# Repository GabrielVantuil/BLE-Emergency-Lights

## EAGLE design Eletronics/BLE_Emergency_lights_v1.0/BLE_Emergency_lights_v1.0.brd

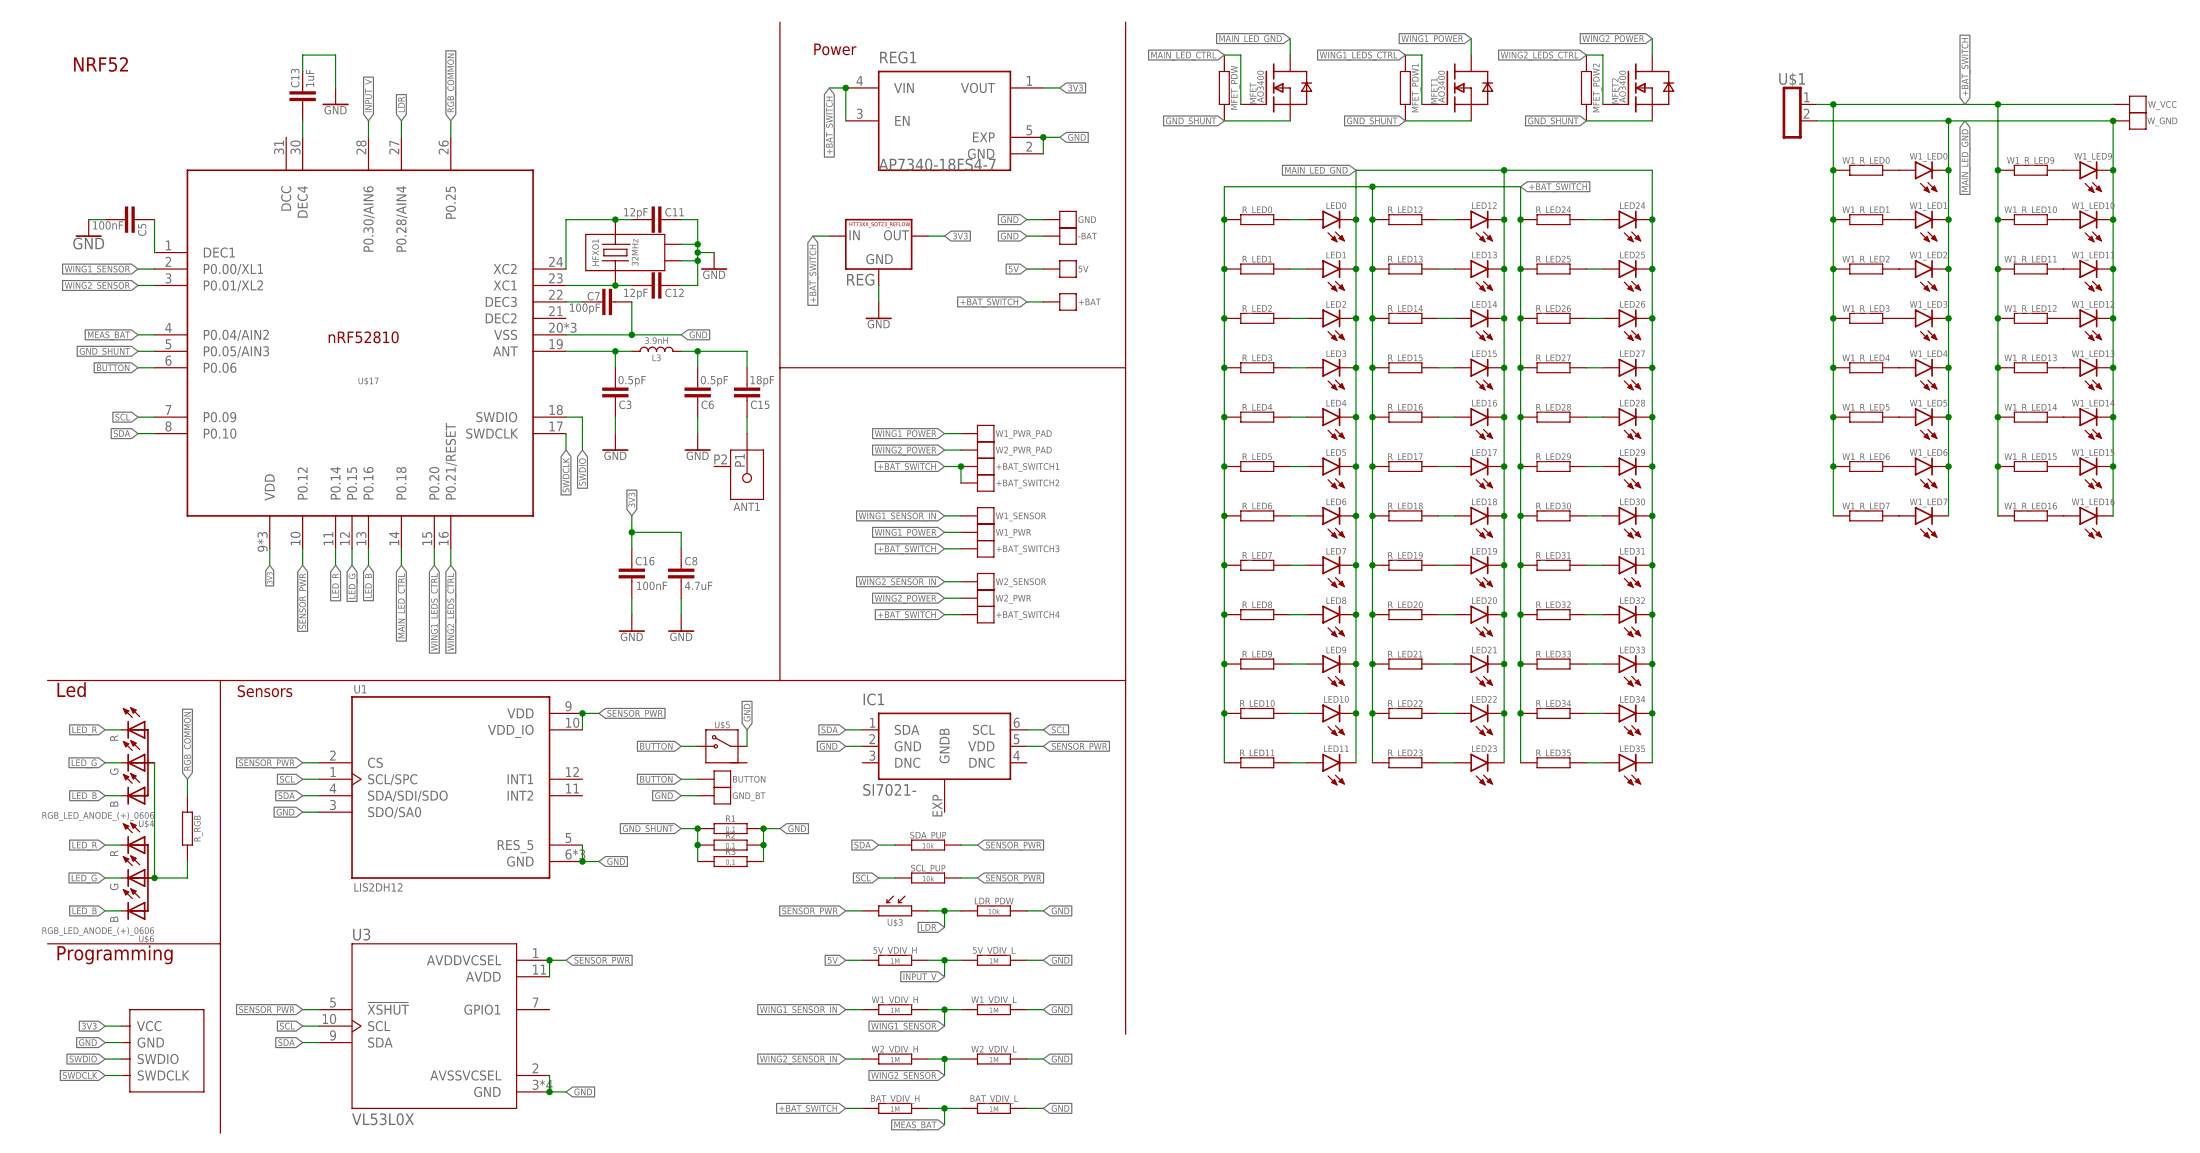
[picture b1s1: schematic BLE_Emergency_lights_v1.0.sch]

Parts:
5V: PAD_50X100MIL
5V_VDIV_H, 5V_VDIV_L: 1M; 0402-RES
+BAT: PAD_50X100MIL
+BAT_SWITCH1, +BAT_SWITCH2: PAD_50X100MIL
+BAT_SWITCH3, +BAT_SWITCH4: SMD_VERTICAL_POGOPIN_0.8MM; POGOPIN_0.8T
-BAT: PAD_50X100MIL
ANT1: ANT3216LL00R2400A
BAT_VDIV_H: 1M; 0402-RES
BAT_VDIV_L: 1M; 0402-RES
BUTTON: PAD_50X100MIL
C3, C6: 0.5pF; 0201_LARGE_FP-CAP
C5, C16: 100nF; 0201_LARGE_FP-CAP
C7: 100pF; 0201_LARGE_FP-CAP
C8: 4.7uF; 0402-CAP
C11, C12: 12pF; 0201_LARGE_FP-CAP
C13: 1uF; 0201_LARGE_FP-CAP
C15: 18pF; 0201_LARGE_FP-CAP
GND: PAD_50X100MIL
GND_BT: PAD_50X100MIL
HFXO1: 32MHz; XTAL_CX2016DB16000D0WZRC1
IC1: SI7021-; DFN6-3X3
L3: 3.9nH; 0201_LARGE_FP-CAP
LDR_PDW: 10k; 0402-RES
LED0, LED1, LED2, LED3, LED4, LED5, LED6, LED7, LED8, LED9, LED10, LED11, LED12, LED13, LED14, LED15, LED16, LED17, LED18, LED19, LED20, LED21, LED22, LED23, LED24, LED25, LED26, LED27, LED28, LED29, LED30, LED31, LED32, LED33, LED34, LED35: LED_1210; 1210
MFET, MFET1, MFET2: AO3400; SOT23-3
MFET_PDW, MFET_PDW1, MFET_PDW2: RESISTOR0402-RES; 0402-RES
R1, R2, R3: 0,1; 1206
REG: HT73XX_SOT23_REFLOW; SOT23-R
REG1: AP7340-18FS4-7; VREG_AP7340-18FS4-7
R_LED0, R_LED1, R_LED2, R_LED3, R_LED4, R_LED5, R_LED6, R_LED7, R_LED8, R_LED9, R_LED10, R_LED11, R_LED12, R_LED13, R_LED14, R_LED15, R_LED16, R_LED17, R_LED18, R_LED19, R_LED20, R_LED21, R_LED22, R_LED23, R_LED24, R_LED25, R_LED26, R_LED27, R_LED28, R_LED29, R_LED30, R_LED31, R_LED32, R_LED33, R_LED34, R_LED35: RESISTOR0603-RES; 0603-RES
R_RGB: RESISTOR_0201_LARGE_FP; 0201_LARGE_FT-RES
SCL_PUP: 10k; 0402-RES
SDA_PUP: 10k; 0402-RES
U1: LIS2DH12; SENSOR_LIS2DH12
U3: VL53L0X; SENSOR_VL53L0X
U$1: RING_PAD_02_4X6; 2X_RING_PAD_4X6
U$3: LDR_5MM
U$4, U$6: RGB_LED_ANODE_(+)_0606; LED_RGB_0606
U$5: PUSHBUTTON_2X4X3.5; 2X4X3.5MM
U$9: GV_SWD_4P; GV_SWD_1.27MM_4P_SEMI_SMD
U$17: NRF52810-QFN32; QFN32-SMALL_PADS2
W1_LED0, W1_LED1, W1_LED2, W1_LED3, W1_LED4, W1_LED5, W1_LED6, W1_LED7, W1_LED9, W1_LED10, W1_LED11, W1_LED12, W1_LED13, W1_LED14, W1_LED15, W1_LED16: LED_1210; 1210
W1_PWR, W1_SENSOR, W2_PWR, W2_SENSOR: SMD_VERTICAL_POGOPIN_0.8MM; POGOPIN_0.8T
W1_PWR_PAD, W2_PWR_PAD: PAD_50X100MIL
W1_R_LED0, W1_R_LED1, W1_R_LED2, W1_R_LED3, W1_R_LED4, W1_R_LED5, W1_R_LED6, W1_R_LED7, W1_R_LED9, W1_R_LED10, W1_R_LED11, W1_R_LED12, W1_R_LED13, W1_R_LED14, W1_R_LED15, W1_R_LED16: RESISTOR0603-RES; 0603-RES
W1_VDIV_H, W1_VDIV_L, W2_VDIV_H, W2_VDIV_L: 1M; 0402-RES
W_GND: PINH1X01_0.8MM; 0.8MM
W_VCC: PINH1X01_0.8MM; 0.8MM

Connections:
3V3: C8.1, C16.1, REG.2 (3.OUT), REG1.1 (VOUT), U$9.VCC, U$17.9 (VDD), U$17.25 (VDD), U$17.32 (VDD)
5V: 5V.P$1, 5V_VDIV_H.2
+BAT_SWITCH: +BAT.P$1, +BAT_SWITCH1.P$1, +BAT_SWITCH2.P$1, +BAT_SWITCH3.P$1, +BAT_SWITCH4.P$1, BAT_VDIV_H.2, REG.3 (1.IN), REG1.3 (EN), REG1.4 (VIN), R_LED0.1, R_LED1.1, R_LED2.1, R_LED3.1, R_LED4.1, R_LED5.1, R_LED6.1, R_LED7.1, R_LED8.1, R_LED9.1, R_LED10.1, R_LED11.1, R_LED12.1, R_LED13.1, R_LED14.1, R_LED15.1, R_LED16.1, R_LED17.1, R_LED18.1, R_LED19.1, R_LED20.1, R_LED21.1, R_LED22.1, R_LED23.1, R_LED24.1, R_LED25.1, R_LED26.1, R_LED27.1, R_LED28.1, R_LED29.1, R_LED30.1, R_LED31.1, R_LED32.1, R_LED33.1, R_LED34.1, R_LED35.1, U$1.1, W1_R_LED0.1, W1_R_LED1.1, W1_R_LED2.1, W1_R_LED3.1, W1_R_LED4.1, W1_R_LED5.1, W1_R_LED6.1, W1_R_LED7.1, W1_R_LED9.1, W1_R_LED10.1, W1_R_LED11.1, W1_R_LED12.1, W1_R_LED13.1, W1_R_LED14.1, W1_R_LED15.1, W1_R_LED16.1, W_VCC.P$1
ANT1: C3.1, L3.1, U$17.19 (ANT)
ANT2: C6.1, C15.1, L3.2
BUTTON: BUTTON.P$1, U$5.1, U$17.6 (P0.06)
GND: 5V_VDIV_L.2, -BAT.P$1, BAT_VDIV_L.2, C3.2, C5.2, C6.2, C7.1, C8.2, C11.1, C12.1, C13.1, C16.2, GND.P$1, GND_BT.P$1, HFXO1.2, HFXO1.4, IC1.2 (GND), LDR_PDW.2, R1.2, R2.2, R3.2, REG.1 (2.GND), REG1.2 (GND), REG1.5 (EXP), U1.3 (SDO/SA0), U1.5 (RES_5), U1.6 (GND), U1.7 (GND), U1.8 (GND), U3.2 (AVSSVCSEL), U3.3 (GND), U3.4 (GND), U3.6 (GND), U3.12 (GND), U$5.2, U$9.GND, U$17.20 (VSS), U$17.29 (VSS), U$17.EXP (VSS), W1_VDIV_L.2, W2_VDIV_L.2
GND_SHUNT: MFET.2 (S), MFET1.2 (S), MFET2.2 (S), MFET_PDW.2, MFET_PDW1.2, MFET_PDW2.2, R1.1, R2.1, R3.1, U$17.5 (P0.05/AIN3)
INPUT_V: 5V_VDIV_H.1, 5V_VDIV_L.1, U$17.28 (P0.30/AIN6)
LDR: LDR_PDW.1, U$3.P$2, U$17.27 (P0.28/AIN4)
LED_B: U$4.B (LED_BLUE), U$6.B (LED_BLUE), U$17.13 (P0.16)
LED_G: U$4.G (LED_GREEN), U$6.G (LED_GREEN), U$17.12 (P0.15)
LED_R: U$4.R (LED_RED), U$6.R (LED_RED), U$17.11 (P0.14)
MAIN_LED_CTRL: MFET.1 (G), MFET_PDW.1, U$17.14 (P0.18)
MAIN_LED_GND: LED0.C, LED1.C, LED2.C, LED3.C, LED4.C, LED5.C, LED6.C, LED7.C, LED8.C, LED9.C, LED10.C, LED11.C, LED12.C, LED13.C, LED14.C, LED15.C, LED16.C, LED17.C, LED18.C, LED19.C, LED20.C, LED21.C, LED22.C, LED23.C, LED24.C, LED25.C, LED26.C, LED27.C, LED28.C, LED29.C, LED30.C, LED31.C, LED32.C, LED33.C, LED34.C, LED35.C, MFET.3 (D), U$1.2, W1_LED0.C, W1_LED1.C, W1_LED2.C, W1_LED3.C, W1_LED4.C, W1_LED5.C, W1_LED6.C, W1_LED7.C, W1_LED9.C, W1_LED10.C, W1_LED11.C, W1_LED12.C, W1_LED13.C, W1_LED14.C, W1_LED15.C, W1_LED16.C, W_GND.P$1
MEAS_BAT: BAT_VDIV_H.1, BAT_VDIV_L.1, U$17.4 (P0.04/AIN2)
unnamed: ANT1.P1, C15.2
unnamed: C7.2, U$17.22 (DEC3)
unnamed: LED0.A, R_LED0.2
unnamed: C13.2, U$17.30 (DEC4)
unnamed: LED1.A, R_LED1.2
unnamed: R_RGB.2, U$4.COM (COMMON_ANODE), U$6.COM (COMMON_ANODE)
unnamed: LED2.A, R_LED2.2
unnamed: C12.2, HFXO1.3, U$17.23 (XC1)
unnamed: C11.2, HFXO1.1, U$17.24 (XC2)
unnamed: LED3.A, R_LED3.2
unnamed: C5.1, U$17.1 (DEC1)
unnamed: LED4.A, R_LED4.2
unnamed: LED5.A, R_LED5.2
unnamed: LED6.A, R_LED6.2
unnamed: LED7.A, R_LED7.2
unnamed: LED8.A, R_LED8.2
unnamed: LED9.A, R_LED9.2
unnamed: LED10.A, R_LED10.2
unnamed: LED11.A, R_LED11.2
unnamed: LED12.A, R_LED12.2
unnamed: LED13.A, R_LED13.2
unnamed: LED14.A, R_LED14.2
unnamed: LED15.A, R_LED15.2
unnamed: LED16.A, R_LED16.2
unnamed: LED17.A, R_LED17.2
unnamed: LED18.A, R_LED18.2
unnamed: LED19.A, R_LED19.2
unnamed: LED20.A, R_LED20.2
unnamed: LED21.A, R_LED21.2
unnamed: LED22.A, R_LED22.2
unnamed: LED23.A, R_LED23.2
unnamed: LED24.A, R_LED24.2
unnamed: LED25.A, R_LED25.2
unnamed: LED26.A, R_LED26.2
unnamed: LED27.A, R_LED27.2
unnamed: LED28.A, R_LED28.2
unnamed: LED29.A, R_LED29.2
unnamed: LED30.A, R_LED30.2
unnamed: LED31.A, R_LED31.2
unnamed: LED32.A, R_LED32.2
unnamed: LED33.A, R_LED33.2
unnamed: LED34.A, R_LED34.2
unnamed: LED35.A, R_LED35.2
unnamed: W1_LED0.A, W1_R_LED0.2
unnamed: W1_LED1.A, W1_R_LED1.2
unnamed: W1_LED2.A, W1_R_LED2.2
unnamed: W1_LED3.A, W1_R_LED3.2
unnamed: W1_LED4.A, W1_R_LED4.2
unnamed: W1_LED5.A, W1_R_LED5.2
unnamed: W1_LED6.A, W1_R_LED6.2
unnamed: W1_LED7.A, W1_R_LED7.2
unnamed: W1_LED9.A, W1_R_LED9.2
unnamed: W1_LED10.A, W1_R_LED10.2
unnamed: W1_LED11.A, W1_R_LED11.2
unnamed: W1_LED12.A, W1_R_LED12.2
unnamed: W1_LED13.A, W1_R_LED13.2
unnamed: W1_LED14.A, W1_R_LED14.2
unnamed: W1_LED15.A, W1_R_LED15.2
unnamed: W1_LED16.A, W1_R_LED16.2
RGB_COMMON: R_RGB.1, U$17.26 (P0.25)
SCL: IC1.6 (SCL), SCL_PUP.1, U1.1 (SCL/SPC), U3.10 (SCL), U$17.7 (P0.09)
SDA: IC1.1 (SDA), SDA_PUP.1, U1.4 (SDA/SDI/SDO), U3.9 (SDA), U$17.8 (P0.10)
SENSOR_PWR: IC1.5 (VDD), SCL_PUP.2, SDA_PUP.2, U1.2 (CS), U1.9 (VDD), U1.10 (VDD_IO), U3.1 (AVDDVCSEL), U3.5 (!XSHUT), U3.11 (AVDD), U$3.P$1, U$17.10 (P0.12)
SWDCLK: U$9.SWDCLK, U$17.17 (SWDCLK)
SWDIO: U$9.SWDIO, U$17.18 (SWDIO)
WING1_LEDS_CTRL: MFET1.1 (G), MFET_PDW1.1, U$17.15 (P0.20)
WING1_POWER: MFET1.3 (D), W1_PWR.P$1, W1_PWR_PAD.P$1
WING1_SENSOR: U$17.2 (P0.00/XL1), W1_VDIV_H.1, W1_VDIV_L.1
WING1_SENSOR_IN: W1_SENSOR.P$1, W1_VDIV_H.2
WING2_LEDS_CTRL: MFET2.1 (G), MFET_PDW2.1, U$17.16 (P0.21/RESET)
WING2_POWER: MFET2.3 (D), W2_PWR.P$1, W2_PWR_PAD.P$1
WING2_SENSOR: U$17.3 (P0.01/XL2), W2_VDIV_H.1, W2_VDIV_L.1
WING2_SENSOR_IN: W2_SENSOR.P$1, W2_VDIV_H.2

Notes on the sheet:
NRF52
Led
Sensors
Power
Programming

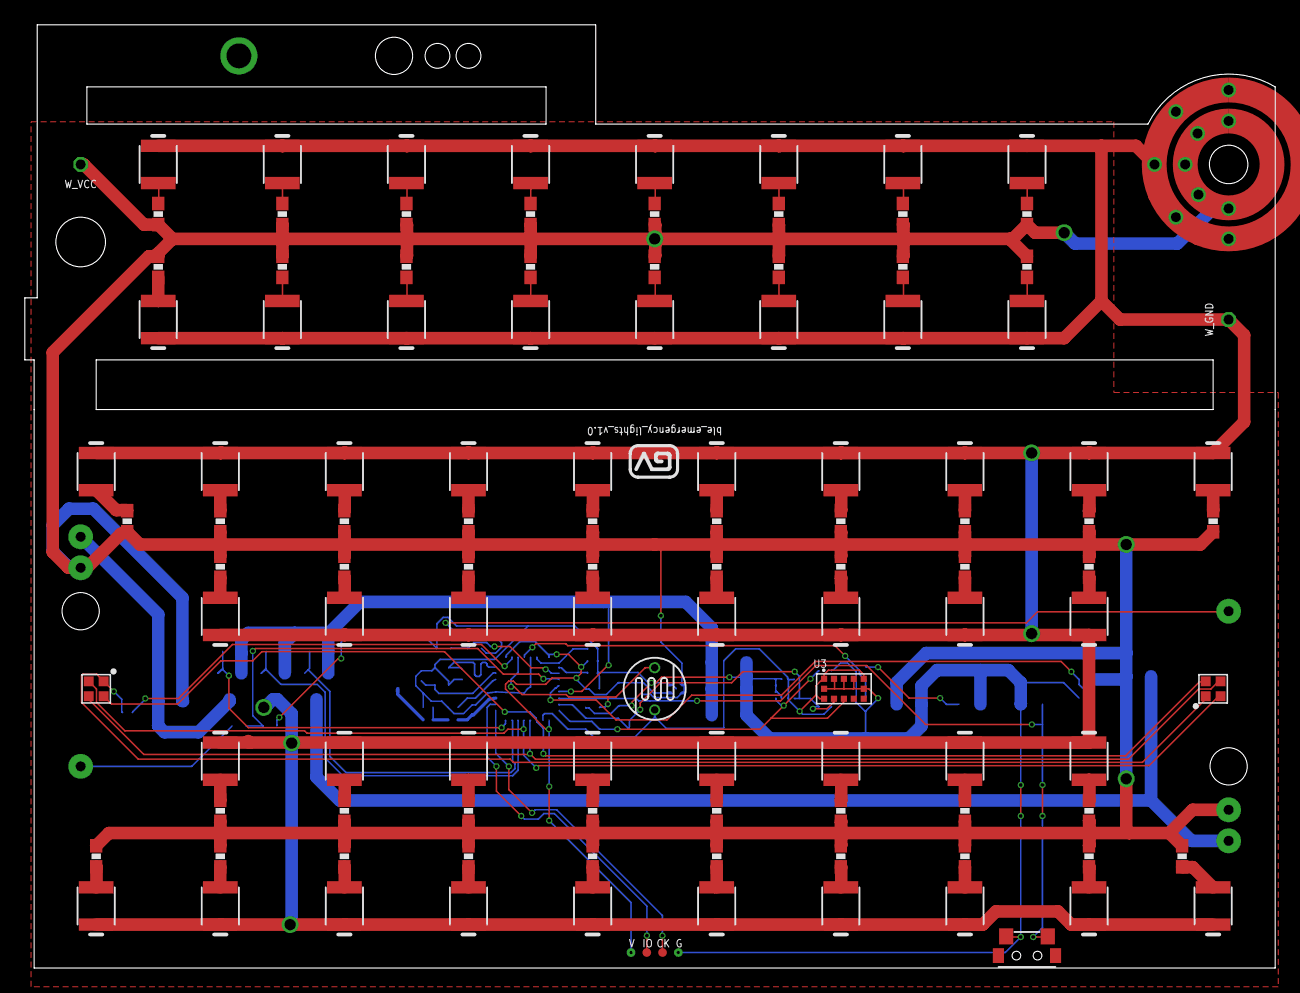
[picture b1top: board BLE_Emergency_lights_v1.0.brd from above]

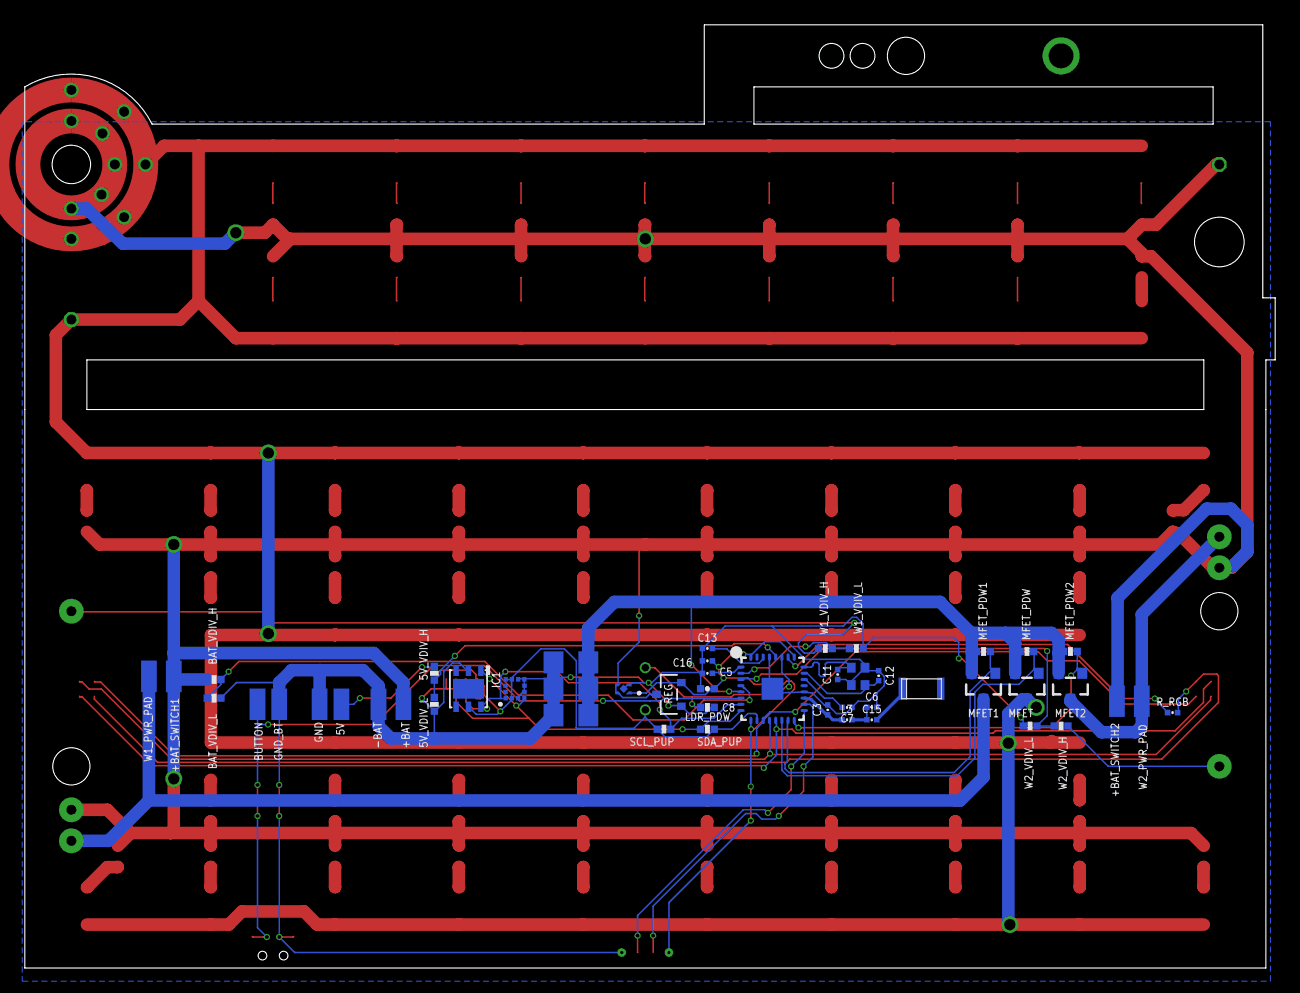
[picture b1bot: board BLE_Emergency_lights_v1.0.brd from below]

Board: 2 copper layers, 100.8 x 76.0 mm, 169 parts (51 on the bottom side), 89 nets.

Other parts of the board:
U$2: GV_5MM

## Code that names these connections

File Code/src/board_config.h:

#ifndef BOARD_CONFIG_H
#define BOARD_CONFIG_H

#define LED_ON	1
#define LED_OFF	0

//#define LED_CTRL_PIN    18
//#define IR_SENSOR_PIN   5 //AIN3
//#define IR_LED_PIN      0

#define WING1_PIN	   	00
#define WING2_PIN	   	01

#define MEAS_BAT_PIN    04
#define SHUNT_PIN	   	05
#define BUTTON_PIN	   	06

#define SCL_PIN	       	09
#define SDA_PIN		   	10

#define SENSOR_PWR_PIN	12

#define LED_R_PIN      	14
#define LED_G_PIN      	15
#define LED_B_PIN      	16

#define MAIN_LED_CTRL_PIN    18
#define WING1_LED_CTRL_PIN   20
#define WING2_LED_CTRL_PIN   21

#define INPUT_V_PIN     30
#define LDR_PIN         28
#define RGB_COMMON_PIN  25

#define VBAT_SAADC_CH		0
#define LED_SHUNT_SAADC_CH	1
#define VDD_SAADC_CH		2

#define VBAT_APIN 		NRF_SAADC_INPUT_AIN2
#define LED_SHUNT_APIN 	NRF_SAADC_INPUT_AIN3


#endif

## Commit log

2025-02-08 BLE_Emergency_lights_v1.0
2025-05-21 First (simple) working code
2025-05-21 CAD for board v1.0
2025-05-26 Applying pwm to the wings as well (not currently using due to lack of control over them)
2025-10-26 CAD new version
2026-02-08 Refactoring and adding voltage check
